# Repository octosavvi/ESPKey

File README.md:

### What the heck is this anyway?
ESPKey is a small device which can be implanted into facility access control systems.  ESPKey is compatible with pretty much every door that requires a card swipe or tap with optional pin code to unlock.  It even works on many systems requiring finger print or other biometric authentication.  Inserting an ESPKey behind a card reader is better than a skimmer because not only can it log all authorized use of a system, it can also inject or replay captured credentials.  Once ESPKey shows you what credentials work on this door, use your favorite RFID tools to clone or simulate those credentials for use on other doors.  Want to show someone how insecure their facility is?  This is an incredibly easy way to start.

In case you need a simple access control system to play with, ESPKey can do that too.  All you need is a card reader, ESPKey and some device to be controlled (like a door lock, electric strike, magnetic lock or just an indicator light).  ESPKey replaces the giant door controller, allowing you to build a simple mobile test lab.  Or a great little portable RFID credential sponge, ready to be hand carried or installed in any heavily trafficked area.

### Releases
Have a look [over here](https://github.com/octosavvi/ESPKey/releases/latest) for the latest pre-built firmware and UI release.

### Build instructions
1. [Install PlatformIO Core](http://docs.platformio.org/page/core.html)
2.  Run these commands:

```shell
# Change to working directory
$ cd <path-to-workingdir>

# Build project
$ pio run

# Upload firmware
$ pio run --target upload

# Build specific environment
$ pio run -e esp12

# Upload firmware for the specific environment
$ pio run -e esp12 --target upload

# Clean build files
$ pio run --target clean
```

3. Launch html_src/publish.sh to generate ui-update.sh. When connected to ESPKey's web server, launch ui-update.sh to upload the files that make the web UI.

### Usage
Check out [this great documentation](https://redteamtools.com/espkey) put together by Babak of Red Team Tools.

### Hardware
Hardware can be [purchased](https://redteamtools.com/espkey) or have a look in the [hardware](hardware/) directory if you want to build your own.

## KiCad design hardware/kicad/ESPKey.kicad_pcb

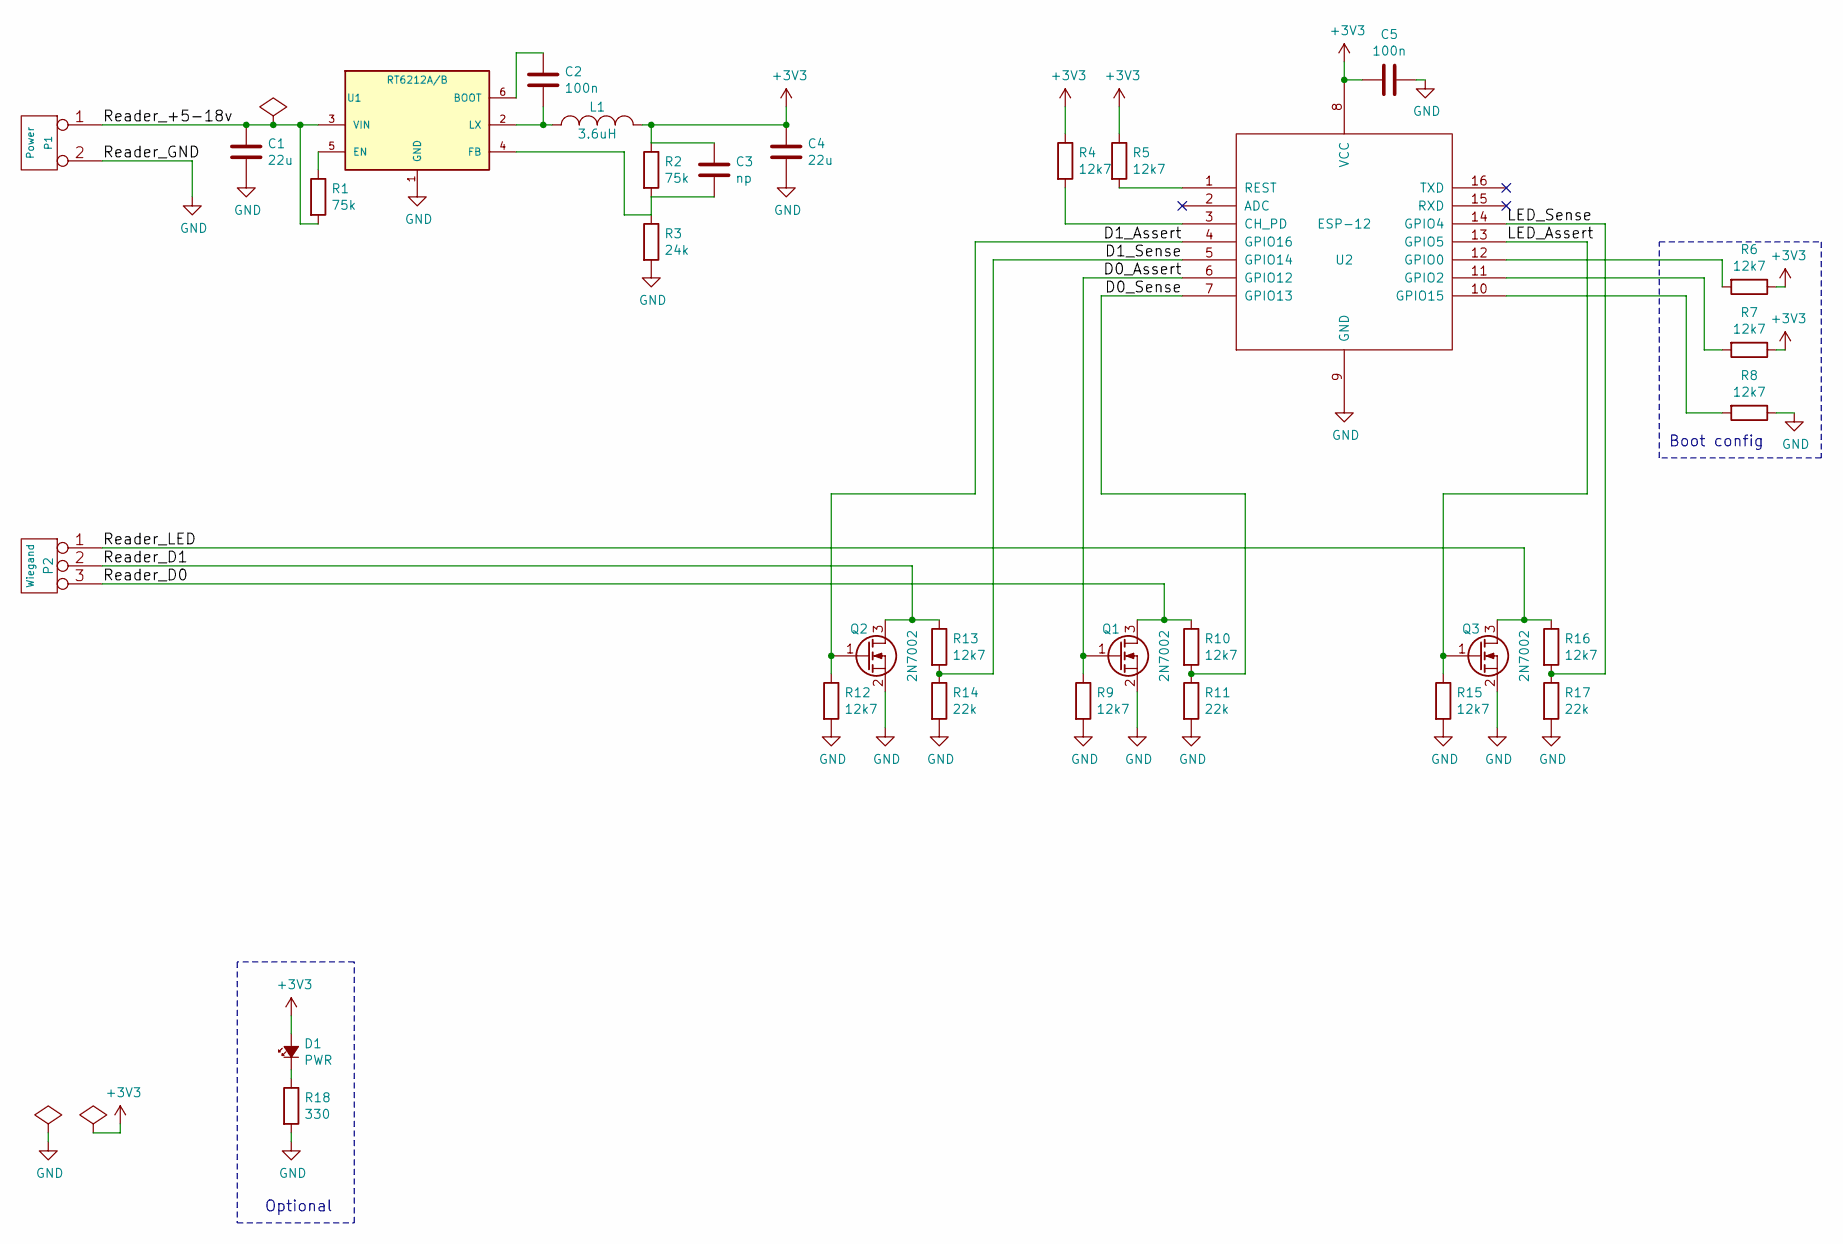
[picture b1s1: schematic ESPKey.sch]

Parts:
C1, C4: 22u; C_0805
C2, C5: 100n; C_0603
C3: np; C_0402
D1: PWR; LED_0603
L1: 3.6uH; ELL4_M-small
P1: Power; SSL_DW_IDC_02
P2: Wiegand; SSL_DW_IDC_03
Q1, Q2, Q3: 2N7002; SOT-23
R1, R2: 75k; R_0402
R3: 24k; R_0402
R4, R5, R6, R7, R8, R9, R10, R12, R13, R15, R16: 12k7; R_0402
R11, R14, R17: 22k; R_0402
R18: 330; R_0402
U1: RT6212A/B; SOT-23-6
U2: ESP-12; ESP-12-SMD

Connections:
+3V3: C3.2, C4.2, C5.2, D1.2 (A), L1.2, R2.1, R4.1, R5.1, R6.1, R7.1, U2.8 (VCC)
/D0_Assert: Q1.1 (G), R9.1, U2.6 (GPIO12)
/D0_Sense: R10.2, R11.1, U2.7 (GPIO13)
/D1_Assert: Q2.1 (G), R12.1, U2.4 (GPIO16)
/D1_Sense: R13.2, R14.1, U2.5 (GPIO14)
/LED_Assert: Q3.1 (G), R15.1, U2.13 (GPIO5)
/LED_Sense: R16.2, R17.1, U2.14 (GPIO4)
/Reader_+5-18v: C1.2, P1.1, R1.2, U1.3 (VIN)
/Reader_D0: P2.3, Q1.3 (D), R10.1
/Reader_D1: P2.2 (PM), Q2.3 (D), R13.1
/Reader_LED: P2.1, Q3.3 (D), R16.1
GND: C1.1, C4.1, C5.1, P1.2 (PM), Q1.2 (S), Q2.2 (S), Q3.2 (S), R3.2, R8.1, R9.2, R11.2, R12.2, R14.2, R15.2, R17.2, R18.2, U1.1 (GND), U2.9 (GND)
unnamed: C2.1, L1.1, U1.2 (LX)
unnamed: C2.2, U1.6 (BOOT)
unnamed: C3.1, R2.2, R3.1, U1.4 (FB)
unnamed: D1.1 (K), R18.1
unnamed: R1.1, U1.5 (EN)
unnamed: R4.2, U2.3 (CH_PD)
unnamed: R5.2, U2.1 (REST)
unnamed: R6.2, U2.12 (GPIO0)
unnamed: R7.2, U2.11 (GPIO2)
unnamed: R8.2, U2.10 (GPIO15)

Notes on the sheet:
Boot config
Optional

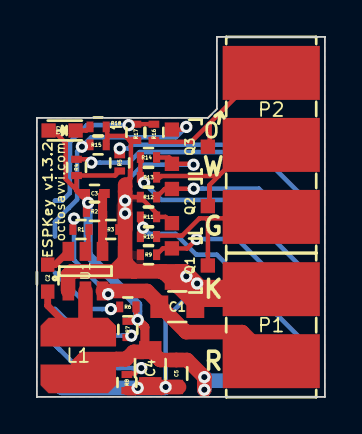
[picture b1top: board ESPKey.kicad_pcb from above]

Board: 2 copper layers, 16.0 x 20.0 mm, 32 parts (1 on the bottom side), 22 nets.

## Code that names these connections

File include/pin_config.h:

// Pin number assignments
// if you change these you may also change the args to createDigigraph() in gpio.htm so the diagnostics tab reflects these changes.
#if defined(ESP8266)

    #define D0_ASSERT 12 
    #define D0_SENSE 13 

    #define D1_ASSERT 16
    #define D1_SENSE 14

    #define LED_ASSERT 4 
    #define LED_SENSE 5

    #define CONF_RESET 0

#elif defined(ESP32)
// for ESP32 you may use GPIO > 31, but the diagnostics graph can't handle them.
    #define D0_ASSERT 33 
    #define D0_SENSE 32 

    #define D1_ASSERT 22
    #define D1_SENSE 35 

    #define LED_ASSERT 23 
    #define LED_SENSE 34 

    #define CONF_RESET 0

#else  
    
    #error "please use ESP8266 or ESP32"

#endif

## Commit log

2018-01-01 Fixing link to hardware directory
2018-01-01 Because the boss says.
2018-01-09 Repair case globbing by removing double-quotes
2018-01-09 Add link to releases which might work
2018-01-09 Fully qualified link to releases
    Nope! A relative link to releases will not do. We want releases, not some blob 404 nonsense!
2018-08-03 Fix UI upload recursion bug when no files are in /
2018-08-03 Check for /log.txt BEFORE writing to it!
2021-08-09 Added schematic PDF
2022-01-05 Dynamically generated by src/publish.sh
2022-01-05 Don't blow away auth.txt on UI update
2022-01-05 Decimal output format with parity bits removed
    This format can be entered directly into some cheap imported handheld
    writers. It is likely to work with 26-bit HID but other formats may work
    too. After some testing, we should rein in when it is displayed.
2022-04-02 Port to ESP32
2022-04-02 Add ace.js locally so we don't need an internet connection when using the UI
2022-04-11 Move to PlatformIO
2022-04-13 Support both ESP32 and ESP8266
2022-04-14 fix possible read out of bonds in loadConfig()
2022-04-14 LED blinking with style
2022-04-14 revert on ace.js (too big for 512k)
2022-07-01 Add ESP-07 configuration
2022-07-01 correct led blink rate on ESP8266
2022-07-01 Add ESP07
2022-10-18 Add pulse width and gap to config
2022-10-18 Add payload column
2022-12-02 Basically just a typo I noticed all debug messages but one are sent to `DBG_OUTPUT_PORT`, which is defined as `Serial`. The outlier directly references `Serial` instead of `DBG_OUTPUT_PORT`. This is 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
2023-05-04 Check for new data every 1 second
